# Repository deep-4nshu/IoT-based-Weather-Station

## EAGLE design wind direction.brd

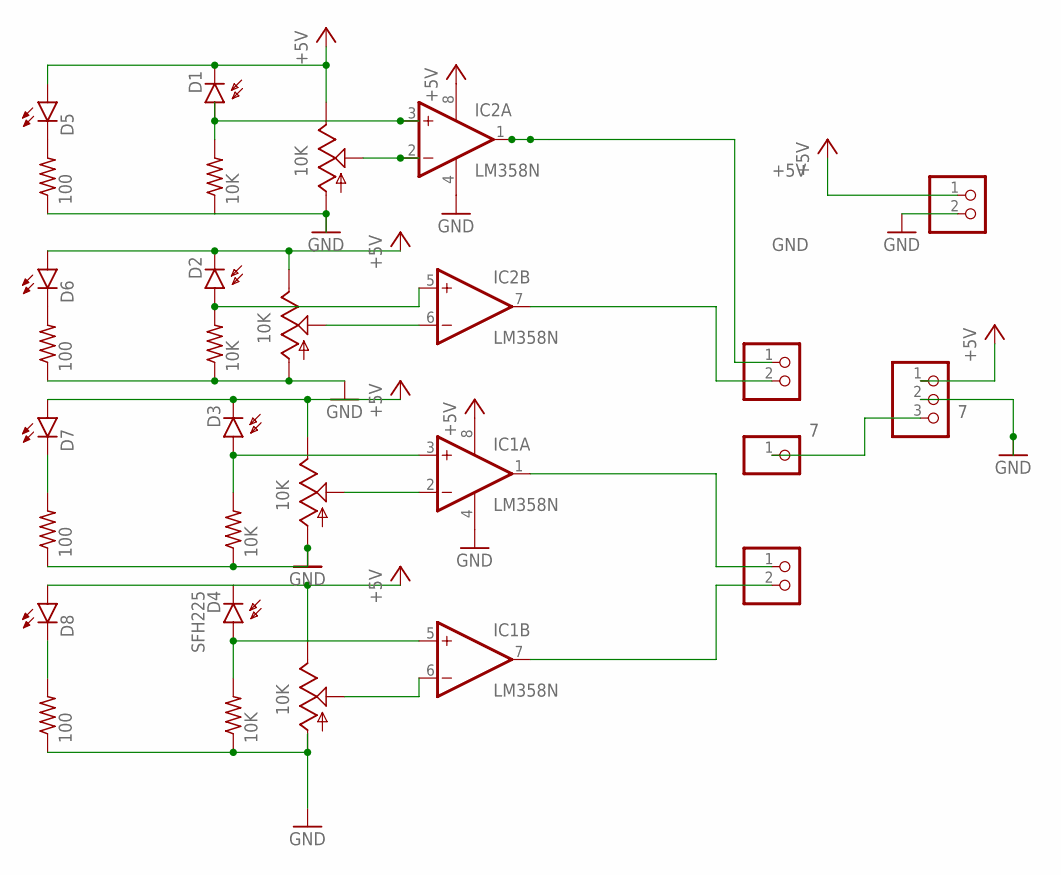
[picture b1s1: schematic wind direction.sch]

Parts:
D1, D2, D3, D4: SFH225
D5, D6, D7, D8: SFH482
IC1, IC2: LM358N; DIL08
JP1, JP2, JP3: PINHD-1X2; 1X02
JP4: PINHD-1X3; 1X03
JP5: PINHD-1X1; 1X01
R1, R3, R5, R8: 10K; 0411/15
R2, R4, R6, R7: 100; 0411/15
R9, R10, R11, R12: 10K; CA14V

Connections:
7: JP4.3, JP5.1
+5V: D1.K (C), D2.K (C), D3.K (C), D4.K (C), D5.A, D6.A, D7.A, D8.A, IC1.8 (V+), IC2.8 (V+), JP2.1, JP4.1, R9.E, R10.E, R11.E, R12.E
GND: IC1.4 (V-), IC2.4 (V-), JP2.2, JP4.2, R1.1, R2.1, R3.1, R4.1, R5.1, R6.1, R7.1, R8.1, R9.A, R10.A, R11.A, R12.A
unnamed: D3.A, IC1.3 (+IN), R5.2
unnamed: D7.K (C), R6.2
unnamed: D2.A, IC2.5 (+IN), R3.2
unnamed: D6.K (C), R4.2
unnamed: D5.K (C), R2.2
unnamed: IC2.2 (-IN), R9.S
unnamed: D1.A, IC2.3 (+IN), R1.2
unnamed: IC2.7 (OUT), JP1.2
unnamed: IC1.1 (OUT), JP3.1
unnamed: IC1.7 (OUT), JP3.2
unnamed: IC2.6 (-IN), R10.S
unnamed: D8.K (C), R7.2
unnamed: IC2.1 (OUT), JP1.1
unnamed: IC1.2 (-IN), R11.S
unnamed: D4.A, IC1.5 (+IN), R8.2
unnamed: IC1.6 (-IN), R12.S

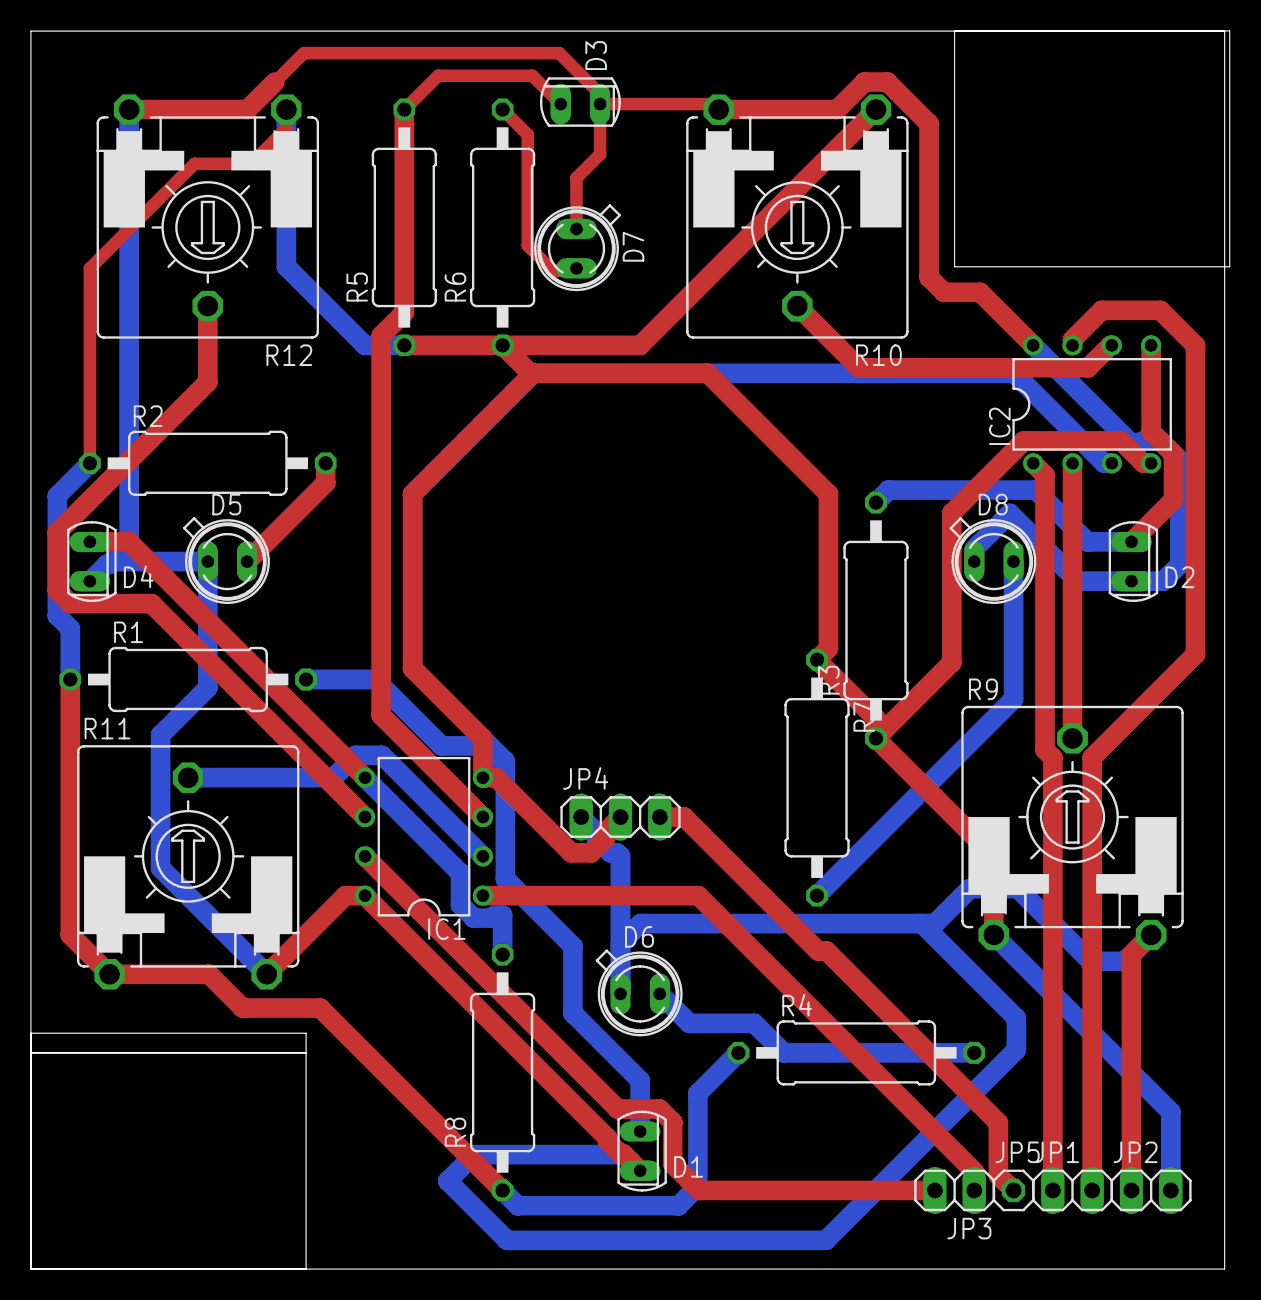
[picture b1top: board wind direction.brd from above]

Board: 2 copper layers, 77.1 x 80.0 mm, 27 parts (0 on the bottom side), 19 nets.
